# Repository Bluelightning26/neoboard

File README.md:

# NeoBoard
## A NeoPixel based PCB Matrix!

*

*Not all time in KiCad and most but not all time in OnShape has been tracked

I made this project as LEDs are fun and Neopixels sit right on the board in a flush, neat way. I wanted a project that can sit on my desk and look cool while being fun and interactive. I started PixelDust but didn't come close to finishing, and figured- why not work on a matrix when waiting for my HackPad (v2) and Solder PCB to ship

**BOM:**
|  Part | #| Cost (Combined) | Supplier  | Link |
|---    |--- |---             |---        | ---  |
|SK6812	| 64 (7 packs of 10) | $34.65 | Digikey | https://www.digikey.com/en/products/detail/adafruit-industries-llc/2659/5804108|
|  EC11E15204A3 | 1  | $4.28 | Digikey |  https://www.digikey.com/en/products/detail/bourns-inc/PEC11R-4215F-S0024/4499665| (https://www.digikey.com/en/products/detail/alps-alpine/EC11E15204A3/21721644)
|XIAO-RP2040-DIP| 1| $4.68| Digikey | https://www.digikey.com/en/products/detail/seeed-technology-co-ltd/102010428/14672129|
| PS1240P02BT| 1 | $0.54|Digikey|https://www.digikey.com/en/products/detail/tdk-corporation/PS1240P02BT/935924
|   C   | 1x ~10uF 10x ~4.7nF | $0.24 + $1.60| Digikey| https://www.digikey.com/en/products/detail/epcos-tdk-electronics/B32529C0102K289/1089737 https://www.digikey.com/en/products/detail/panasonic-electronic-components/ECQ-E4333KF/56549|  
| 330Ohm R | 10 | $0.26 | Digikey | https://www.digikey.com/en/products/detail/stackpole-electronics-inc/CF14JT330R/1741399
|  RE Rubber Knob    | 1 | $0.75| Adafruit | https://www.adafruit.com/product/5093 | 
| 0.91 inch OLED |1 | $1.48 | AliExpress | https://www.aliexpress.us/item/3256809074340394.html|
| PCB Lead Free| 1 | $21.66 (inc shipping) | JLCPCB | https://trade.jlcpcb.com/checkout/
| Case | - | - | Printing Legion | - |
| Small Felt Furniture Feet | 4 | N/A | Already Own | - |

Digikey Shipping: $6.99

AliExpress Shipping: $4.90

**TOTAL: $80.45**

How to put it together?
The top and the bottom of the case can be slid together. I'm going to put felt pads underneath it so the top piece extrudes just slightly lower than the button piece. I was thinking of putting an acrylic sheet on the front to help give it a diffused look, but I'd like the PCB to be easily visable to give it a unique look.

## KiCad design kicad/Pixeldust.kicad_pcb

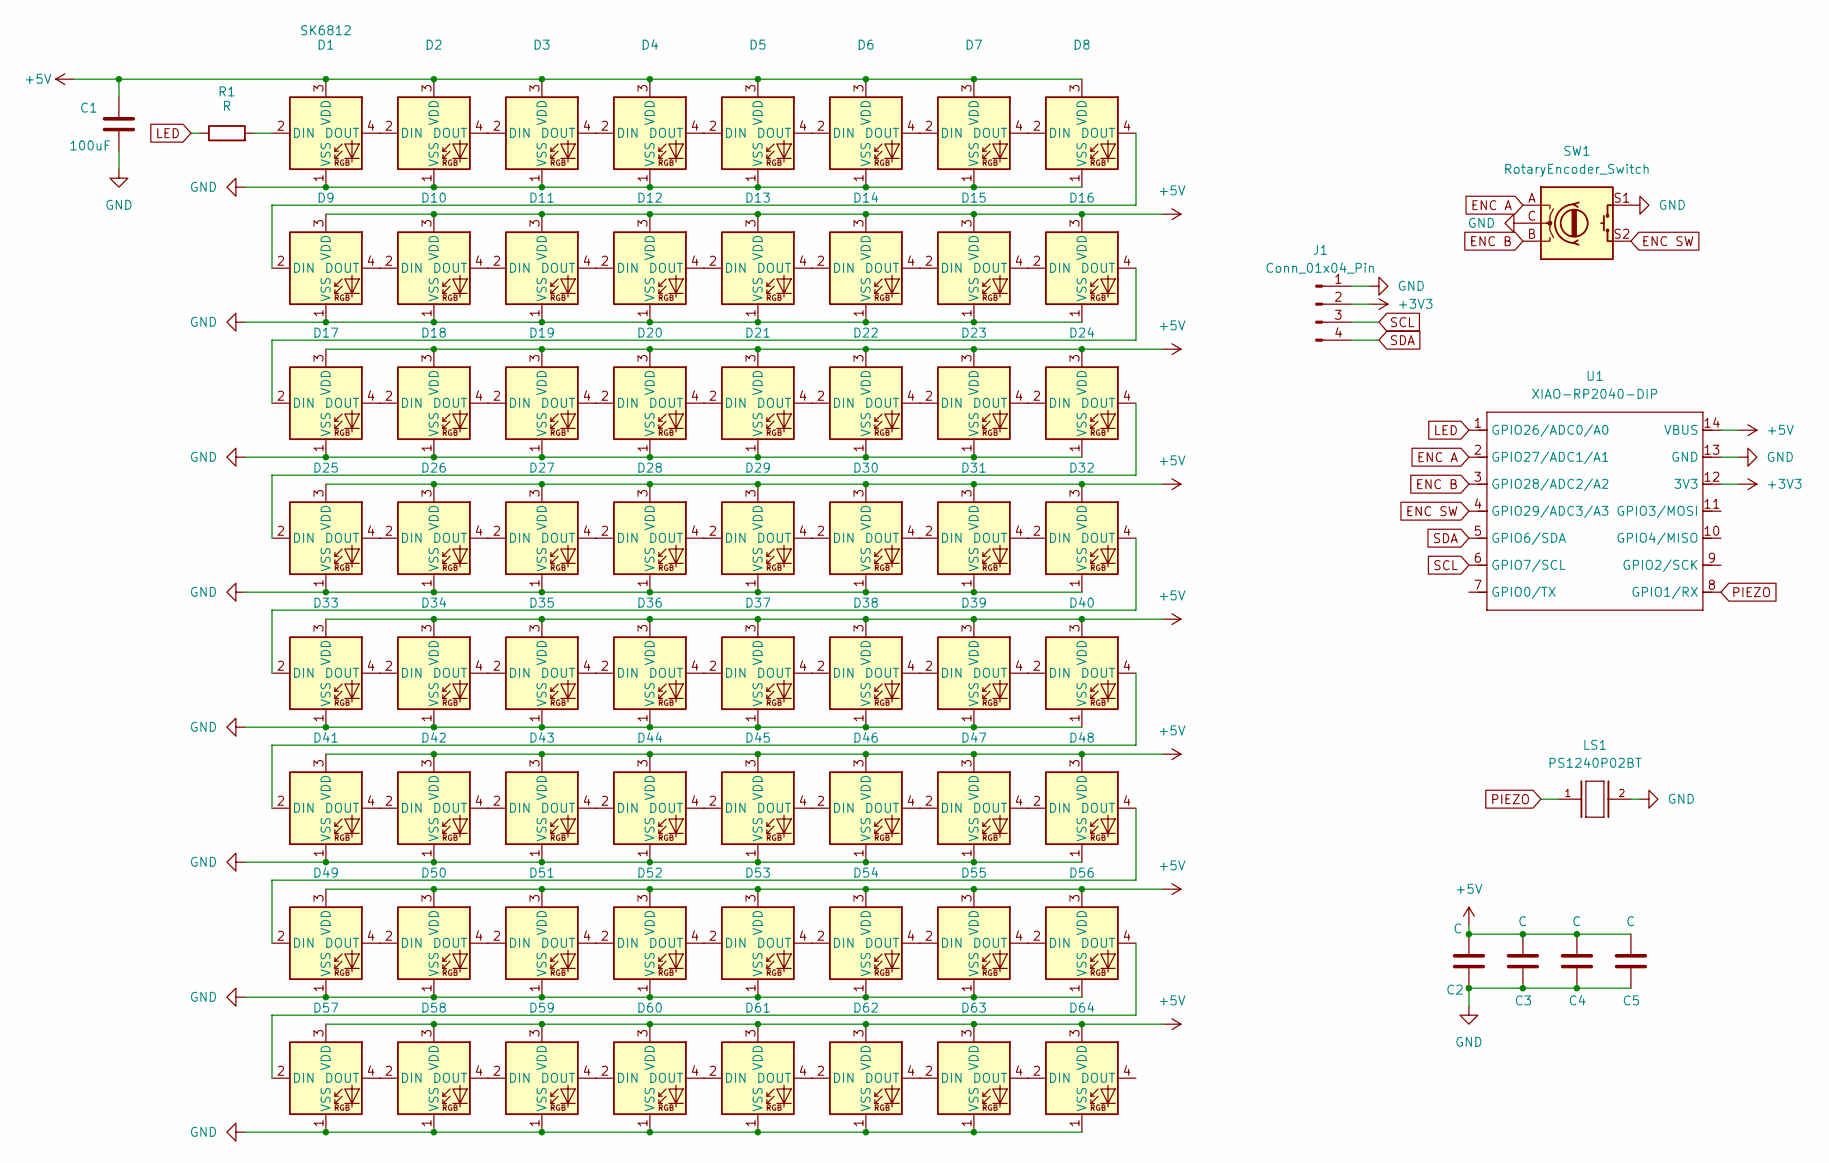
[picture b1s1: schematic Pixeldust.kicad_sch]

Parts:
C1: 100uF; CP_Radial_D8.0mm_P5.00mm
C2, C3, C4, C5: C; CP_Radial_D8.0mm_P5.00mm
D1, D2, D3, D4, D5, D6, D7, D8, D9, D10, D11, D12, D13, D14, D15, D16, D17, D18, D19, D20, D21, D22, D23, D24, D25, D26, D27, D28, D29, D30, D31, D32, D33, D34, D35, D36, D37, D38, D39, D40, D41, D42, D43, D44, D45, D46, D47, D48, D49, D50, D51, D52, D53, D54, D55, D56, D57, D58, D59, D60, D61, D62, D63, D64: SK6812; LED_SK6812_PLCC4_5.0x5.0mm_P3.2mm
J1: Conn_01x04_Pin; SSD1306-0.91-OLED-4pin-128x32
LS1: PS1240P02BT; Buzzer_TDK_PS1240P02BT_D12.2mm_H6.5mm
R1: R; R_Axial_DIN0207_L6.3mm_D2.5mm_P7.62mm_Horizontal
SW1: RotaryEncoder_Switch; RotaryEncoder_Alps_EC12E-Switch_Vertical_H20mm
U1: XIAO-RP2040-DIP

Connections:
+3V3: J1.2, U1.12 (3V3)
+5V: C1.1, C2.1, C3.1, C4.1, C5.1, D1.3 (VDD), D2.3 (VDD), D3.3 (VDD), D4.3 (VDD), D5.3 (VDD), D6.3 (VDD), D7.3 (VDD), D8.3 (VDD), D9.3 (VDD), D10.3 (VDD), D11.3 (VDD), D12.3 (VDD), D13.3 (VDD), D14.3 (VDD), D15.3 (VDD), D16.3 (VDD), D17.3 (VDD), D18.3 (VDD), D19.3 (VDD), D20.3 (VDD), D21.3 (VDD), D22.3 (VDD), D23.3 (VDD), D24.3 (VDD), D25.3 (VDD), D26.3 (VDD), D27.3 (VDD), D28.3 (VDD), D29.3 (VDD), D30.3 (VDD), D31.3 (VDD), D32.3 (VDD), D33.3 (VDD), D34.3 (VDD), D35.3 (VDD), D36.3 (VDD), D37.3 (VDD), D38.3 (VDD), D39.3 (VDD), D40.3 (VDD), D41.3 (VDD), D42.3 (VDD), D43.3 (VDD), D44.3 (VDD), D45.3 (VDD), D46.3 (VDD), D47.3 (VDD), D48.3 (VDD), D49.3 (VDD), D50.3 (VDD), D51.3 (VDD), D52.3 (VDD), D53.3 (VDD), D54.3 (VDD), D55.3 (VDD), D56.3 (VDD), D57.3 (VDD), D58.3 (VDD), D59.3 (VDD), D60.3 (VDD), D61.3 (VDD), D62.3 (VDD), D63.3 (VDD), D64.3 (VDD), U1.14 (VBUS)
ENC A: SW1.A, U1.2 (GPIO27/ADC1/A1)
ENC B: SW1.B, U1.3 (GPIO28/ADC2/A2)
ENC SW: SW1.S2, U1.4 (GPIO29/ADC3/A3)
GND: C1.2, C2.2, C3.2, C4.2, C5.2, D1.1 (VSS), D2.1 (VSS), D3.1 (VSS), D4.1 (VSS), D5.1 (VSS), D6.1 (VSS), D7.1 (VSS), D8.1 (VSS), D9.1 (VSS), D10.1 (VSS), D11.1 (VSS), D12.1 (VSS), D13.1 (VSS), D14.1 (VSS), D15.1 (VSS), D16.1 (VSS), D17.1 (VSS), D18.1 (VSS), D19.1 (VSS), D20.1 (VSS), D21.1 (VSS), D22.1 (VSS), D23.1 (VSS), D24.1 (VSS), D25.1 (VSS), D26.1 (VSS), D27.1 (VSS), D28.1 (VSS), D29.1 (VSS), D30.1 (VSS), D31.1 (VSS), D32.1 (VSS), D33.1 (VSS), D34.1 (VSS), D35.1 (VSS), D36.1 (VSS), D37.1 (VSS), D38.1 (VSS), D39.1 (VSS), D40.1 (VSS), D41.1 (VSS), D42.1 (VSS), D43.1 (VSS), D44.1 (VSS), D45.1 (VSS), D46.1 (VSS), D47.1 (VSS), D48.1 (VSS), D49.1 (VSS), D50.1 (VSS), D51.1 (VSS), D52.1 (VSS), D53.1 (VSS), D54.1 (VSS), D55.1 (VSS), D56.1 (VSS), D57.1 (VSS), D58.1 (VSS), D59.1 (VSS), D60.1 (VSS), D61.1 (VSS), D62.1 (VSS), D63.1 (VSS), D64.1 (VSS), J1.1, LS1.2, SW1.C, SW1.S1, U1.13 (GND)
LED: R1.1, U1.1 (GPIO26/ADC0/A0)
unnamed: D1.2 (DIN), R1.2
unnamed: D1.4 (DOUT), D2.2 (DIN)
unnamed: D2.4 (DOUT), D3.2 (DIN)
unnamed: D3.4 (DOUT), D4.2 (DIN)
unnamed: D4.4 (DOUT), D5.2 (DIN)
unnamed: D5.4 (DOUT), D6.2 (DIN)
unnamed: D6.4 (DOUT), D7.2 (DIN)
unnamed: D7.4 (DOUT), D8.2 (DIN)
unnamed: D8.4 (DOUT), D9.2 (DIN)
unnamed: D9.4 (DOUT), D10.2 (DIN)
unnamed: D10.4 (DOUT), D11.2 (DIN)
unnamed: D11.4 (DOUT), D12.2 (DIN)
unnamed: D12.4 (DOUT), D13.2 (DIN)
unnamed: D13.4 (DOUT), D14.2 (DIN)
unnamed: D14.4 (DOUT), D15.2 (DIN)
unnamed: D15.4 (DOUT), D16.2 (DIN)
unnamed: D16.4 (DOUT), D17.2 (DIN)
unnamed: D17.4 (DOUT), D18.2 (DIN)
unnamed: D18.4 (DOUT), D19.2 (DIN)
unnamed: D19.4 (DOUT), D20.2 (DIN)
unnamed: D20.4 (DOUT), D21.2 (DIN)
unnamed: D21.4 (DOUT), D22.2 (DIN)
unnamed: D22.4 (DOUT), D23.2 (DIN)
unnamed: D23.4 (DOUT), D24.2 (DIN)
unnamed: D24.4 (DOUT), D25.2 (DIN)
unnamed: D25.4 (DOUT), D26.2 (DIN)
unnamed: D26.4 (DOUT), D27.2 (DIN)
unnamed: D27.4 (DOUT), D28.2 (DIN)
unnamed: D28.4 (DOUT), D29.2 (DIN)
unnamed: D29.4 (DOUT), D30.2 (DIN)
unnamed: D30.4 (DOUT), D31.2 (DIN)
unnamed: D31.4 (DOUT), D32.2 (DIN)
unnamed: D32.4 (DOUT), D33.2 (DIN)
unnamed: D33.4 (DOUT), D34.2 (DIN)
unnamed: D34.4 (DOUT), D35.2 (DIN)
unnamed: D35.4 (DOUT), D36.2 (DIN)
unnamed: D36.4 (DOUT), D37.2 (DIN)
unnamed: D37.4 (DOUT), D38.2 (DIN)
unnamed: D38.4 (DOUT), D39.2 (DIN)
unnamed: D39.4 (DOUT), D40.2 (DIN)
unnamed: D40.4 (DOUT), D41.2 (DIN)
unnamed: D41.4 (DOUT), D42.2 (DIN)
unnamed: D42.4 (DOUT), D43.2 (DIN)
unnamed: D43.4 (DOUT), D44.2 (DIN)
unnamed: D44.4 (DOUT), D45.2 (DIN)
unnamed: D45.4 (DOUT), D46.2 (DIN)
unnamed: D46.4 (DOUT), D47.2 (DIN)
unnamed: D47.4 (DOUT), D48.2 (DIN)
unnamed: D48.4 (DOUT), D49.2 (DIN)
unnamed: D49.4 (DOUT), D50.2 (DIN)
unnamed: D50.4 (DOUT), D51.2 (DIN)
unnamed: D51.4 (DOUT), D52.2 (DIN)
unnamed: D52.4 (DOUT), D53.2 (DIN)
unnamed: D53.4 (DOUT), D54.2 (DIN)
unnamed: D54.4 (DOUT), D55.2 (DIN)
unnamed: D55.4 (DOUT), D56.2 (DIN)
unnamed: D56.4 (DOUT), D57.2 (DIN)
unnamed: D57.4 (DOUT), D58.2 (DIN)
unnamed: D58.4 (DOUT), D59.2 (DIN)
unnamed: D59.4 (DOUT), D60.2 (DIN)
unnamed: D60.4 (DOUT), D61.2 (DIN)
unnamed: D61.4 (DOUT), D62.2 (DIN)
unnamed: D62.4 (DOUT), D63.2 (DIN)
unnamed: D63.4 (DOUT), D64.2 (DIN)
PIEZO: LS1.1, U1.8 (GPIO1/RX)
SCL: J1.3, U1.6 (GPIO7/SCL)
SDA: J1.4, U1.5 (GPIO6/SDA)

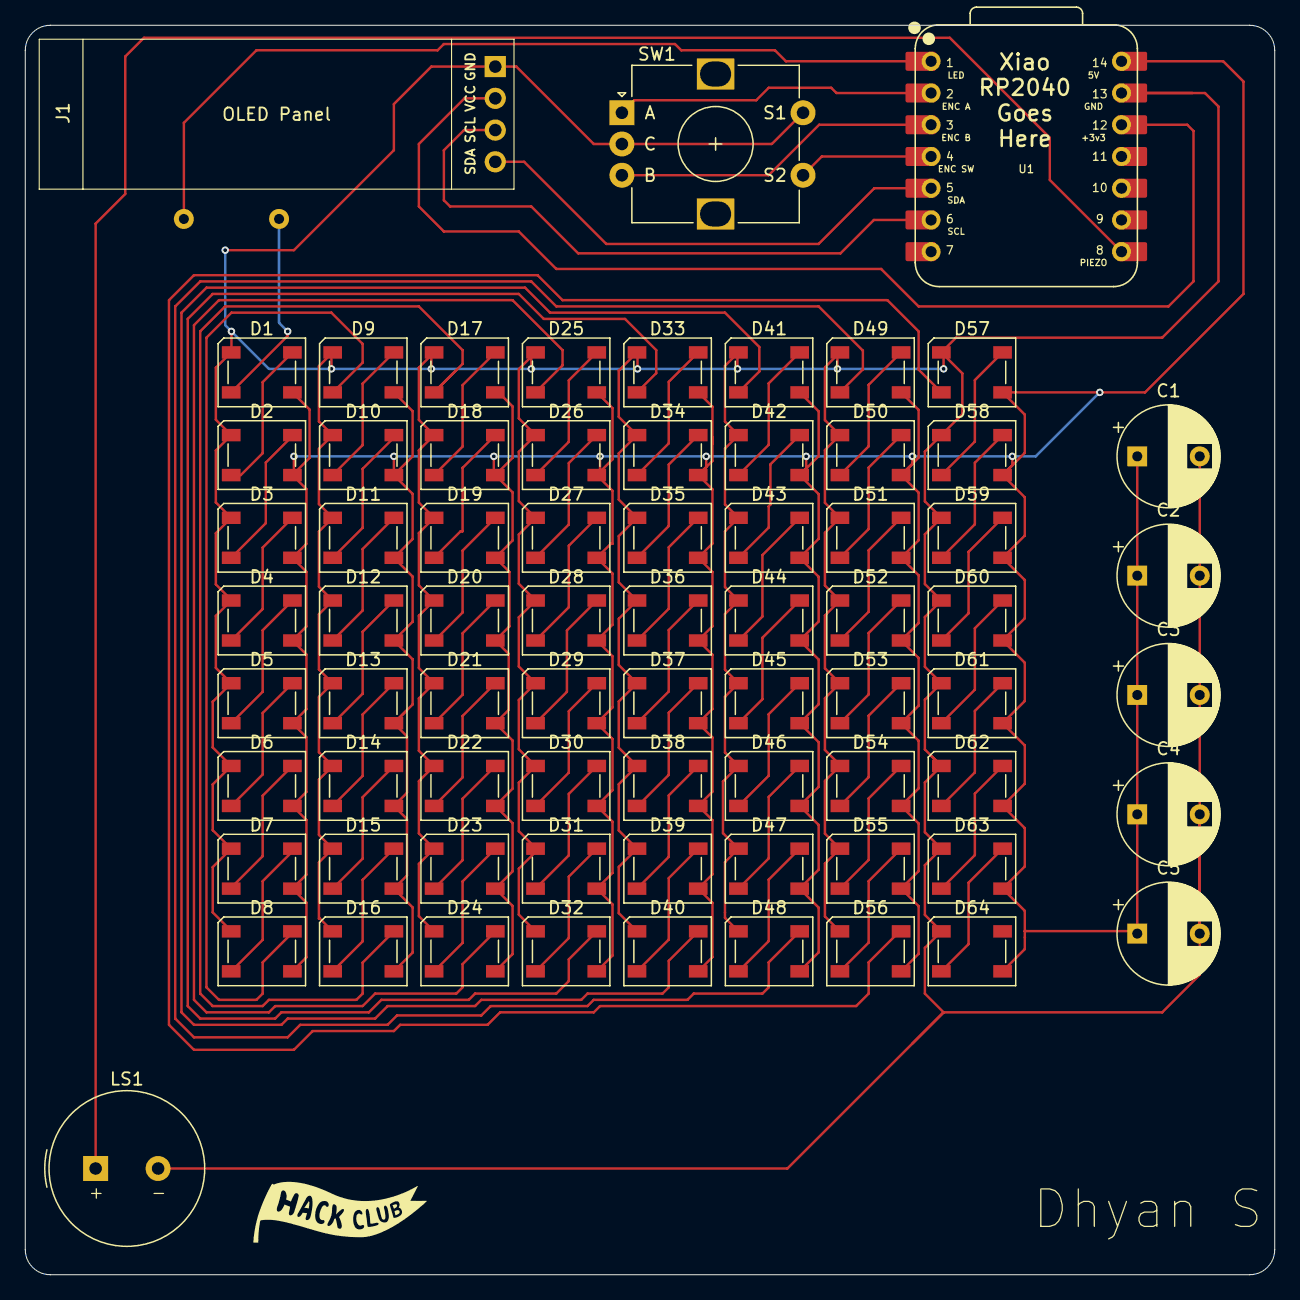
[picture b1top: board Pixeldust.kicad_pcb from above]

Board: 2 copper layers, 100.0 x 100.0 mm, 74 parts (1 on the bottom side), 74 nets.

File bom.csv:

"Id";"Designator";"Footprint";"Quantity";"Designation";"Supplier and ref";
1;"D22,D56,D45,D4,D47,D43,D26,D61,D1,D20,D49,D5,D33,D55,D52,D23,D32,D18,D51,D38,D44,D25,D63,D39,D62,D50,D54,D64,D46,D57,D48,D34,D60,D24,D17,D59,D19,D36,D12,D6,D2,D28,D27,D10,D14,D16,D15,D58,D40,D37,D11,D35,D30,D7,D8,D9,D13,D31,D42,D3,D29,D41,D53,D21";"LED_SK6812_PLCC4_5.0x5.0mm_P3.2mm";64;"SK6812";;;
2;"U1";"XIAO-RP2040-DIP";1;"XIAO-RP2040-DIP";;;
3;"J1";"SSD1306-0.91-OLED-4pin-128x32";1;"Conn_01x04_Pin";;;
4;"C5,C2,C4,C3";"CP_Radial_D8.0mm_P5.00mm";4;"C";;;
5;"SW1";"RotaryEncoder_Alps_EC12E-Switch_Vertical_H20mm";1;"RotaryEncoder_Switch";;;
6;"C1";"CP_Radial_D8.0mm_P5.00mm";1;"100uF";;;
7;"LS1";"Buzzer_TDK_PS1240P02BT_D12.2mm_H6.5mm";1;"PS1240P02BT";;;
8;"R1";"R_Axial_DIN0207_L6.3mm_D2.5mm_P7.62mm_Horizontal";1;"R";;;

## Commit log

2025-06-26 shipping costs
2025-06-27 update case
2025-06-28 journal
